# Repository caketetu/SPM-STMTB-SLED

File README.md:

# SPM-STMTB-SLED

## 概要

SPM-STMTBを使用したフルカラーLED御ボード。LEDポートは4ch実装した。
SK6812フルカラーLEDにて動作を確認

## 機能

* 4chのフルカラーLED制御信号を出力
* 1chあたり最大32LEDの接続
* バッファ書き込みモード
* 全LED同時制御モード
* 三種類のサンプルモード
* RS485,CANインターフェース
* Enable信号入力によるLED制御の上書き

## ピンアサイン
| Function       | Pin  | 備考 |
| -------------- | ---- | ---- |
| TIM1_CH1       | PA0  |   LED_OUT1   |
| TIM1_CH2       | PA1  |   LED_OUT2   |
| USART2_TX      | PA2  |   SYS-RS485   |
| TIM1_CH4     | PA3  |   LED_OUT4   |
| GPIO_Input     | PA4  |      |
| SPI1_SCK       | PA5  |   SYS-SPI   |
| SPI1_MISO      | PA6  |   SYS-SPI   |
| SPI1_MOSI      | PA7  |   SYS-SPI   |
| TIM1_CH1       | PA8  |      |
| USART1_TX      | PA9  |  SYS-UART    |
| USART1_RX      | PA10 |  SYS-UART    |
| FDCAN1_RX      | PA11 |  SYS-CANFD    |
| FDCAN1_TX      | PA12 |  SYS-CANFD    |
| DEBUG_SWDIO    | PA13 |  SYS-DEBUG    |
| DEBUG_SWCLK    | PA14 |  SYS-DEBUG    |
| USART2_RX      | PA15 |  SYS-RS485    |
| SPI1_NSS       | PB0  |  SYS-SPI    |
| GPIO_Output    | PB1  |      |
| GPIO_Output    | PB2  |     |
| GPIO_Output    | PB3  |      |
| GPIO_Output    | PB4  |  SYS-LED1    |
| GPIO_Input     | PB5  |  SYS-EN    |
| TIM1_CH3    | PB6  |  LED_OUT3    |
| GPIO_Output    | PB7  |      |
| GPIO_Output    | PB8  |      |
| GPIO_Input     | PB9  |      |
| GPIO_Output    | PC6  |   SYS-LED0    |
| RCC_OSCIN      | PC14 |   SYS-CLOCK   |
| RCC_OSCOUT     | PC15 |   SYS-CLOCK   |
| RCC_MCO        | PF2  |   SYS-DEBUG   |

※SYS-はSPM共通インターフェース

## 開発環境

| 項目       | 内容                      |
| -------- | ----------------------- |
| MCU      | STM32C092KBT6           |
| IDE      | STM32CubeIDE for VSCode |
| CubeMX   | STM32CubeMX 6.15.0      |
| Firmware | STM32CubeC0             |
| Language | C                       |

## 実装予定機能

* [ ] 4chぶんのバッファ制御

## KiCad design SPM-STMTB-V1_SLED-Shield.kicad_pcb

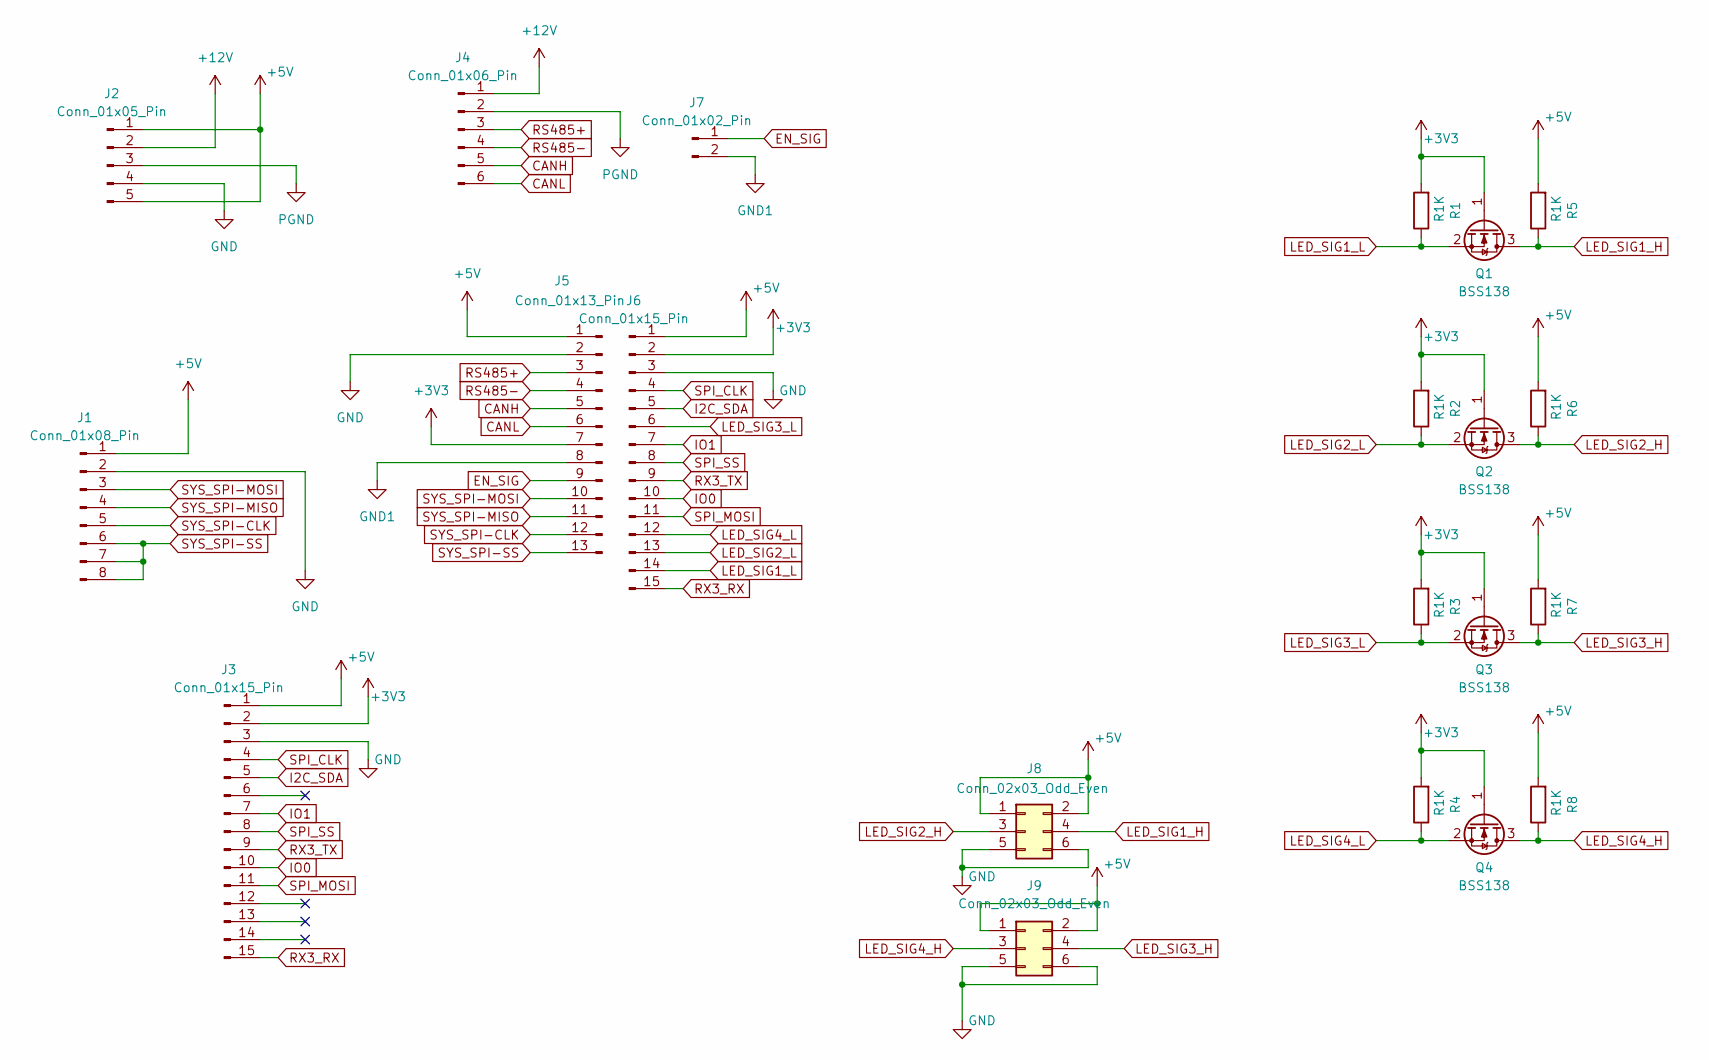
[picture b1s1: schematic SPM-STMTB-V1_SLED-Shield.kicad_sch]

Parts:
J1: Conn_01x08_Pin; PinSocket_1x08_P2.54mm_Vertical
J2: Conn_01x05_Pin; PinSocket_1x05_P2.54mm_Vertical
J3, J6: Conn_01x15_Pin; PinSocket_1x15_P2.54mm_Vertical
J4: Conn_01x06_Pin; PinHeader_1x06_P2.54mm_Vertical
J5: Conn_01x13_Pin; PinSocket_1x13_P2.54mm_Vertical
J7: Conn_01x02_Pin; PinSocket_1x02_P2.54mm_Vertical
J8, J9: Conn_02x03_Odd_Even; PinHeader_2x03_P2.54mm_Horizontal
Q1, Q2, Q3, Q4: BSS138; SOT-23
R1, R2, R3, R4, R5, R6, R7, R8: R1K; R_0603_1608Metric

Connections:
+3V3: J3.2, J5.7, J6.2, Q1.1 (G), Q2.1 (G), Q3.1 (G), Q4.1 (G), R1.2, R2.2, R3.2, R4.2
+5V: J1.1, J2.1, J2.5, J3.1, J5.1, J6.1, J8.1, J8.2, J9.1, J9.2, R5.2, R6.2, R7.2, R8.2
+12V: J2.2, J4.1
CANH: J4.5, J5.5
CANL: J4.6, J5.6
EN_SIG: J5.9, J7.1
GND: J1.2, J2.4, J3.3, J5.2, J6.3, J8.5, J8.6, J9.5, J9.6
GND1: J5.8, J7.2
I2C_SDA: J3.5, J6.5
IO0: J3.10, J6.10
IO1: J3.7, J6.7
LED_SIG1_H: J8.4, Q1.3 (D), R5.1
LED_SIG1_L: J6.14, Q1.2 (S), R1.1
LED_SIG2_H: J8.3, Q2.3 (D), R6.1
LED_SIG2_L: J6.13, Q2.2 (S), R2.1
LED_SIG3_H: J9.4, Q3.3 (D), R7.1
LED_SIG3_L: J6.6, Q3.2 (S), R3.1
LED_SIG4_H: J9.3, Q4.3 (D), R8.1
LED_SIG4_L: J6.12, Q4.2 (S), R4.1
PGND: J2.3, J4.2
RS485+: J4.3, J5.3
RS485-: J4.4, J5.4
RX3_RX: J3.15, J6.15
RX3_TX: J3.9, J6.9
SPI_CLK: J3.4, J6.4
SPI_MOSI: J3.11, J6.11
SPI_SS: J3.8, J6.8
SYS_SPI-CLK: J1.5, J5.12
SYS_SPI-MISO: J1.4, J5.11
SYS_SPI-MOSI: J1.3, J5.10
SYS_SPI-SS: J1.6, J1.7, J1.8, J5.13

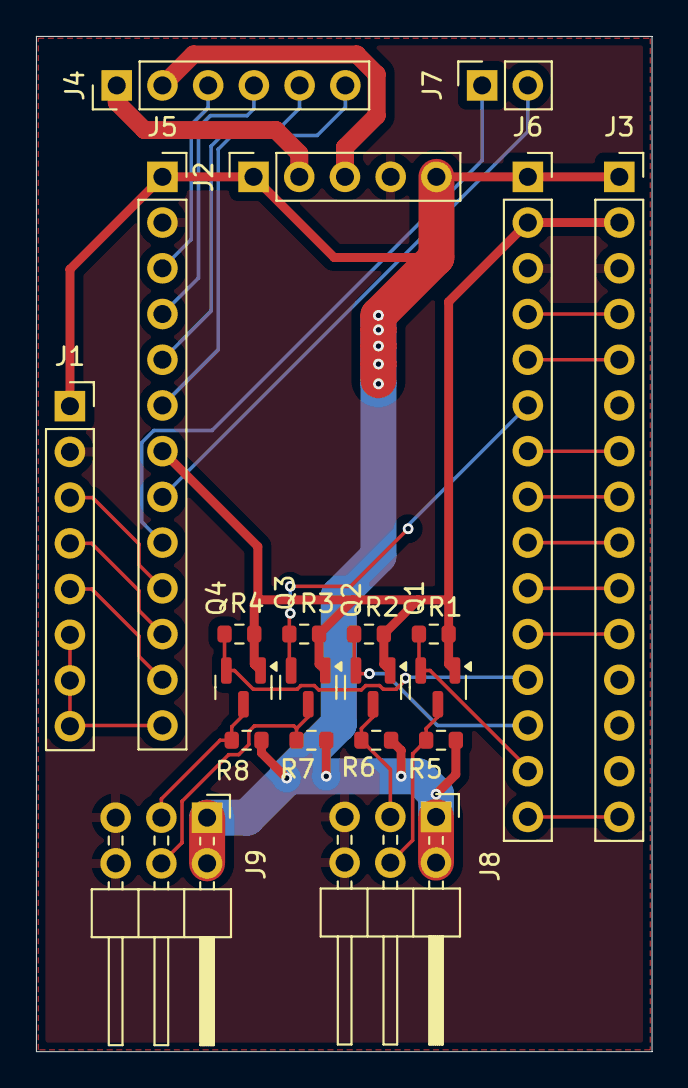
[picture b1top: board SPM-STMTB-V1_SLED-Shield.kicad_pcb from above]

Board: 2 copper layers, 34.2 x 56.4 mm, 21 parts (0 on the bottom side), 31 nets.
